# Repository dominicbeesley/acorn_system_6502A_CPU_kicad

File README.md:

# acorn_system_6502A_CPU_kicad
 Acorn System 6502A clone card

 This is a clone of the Acorn 6502A 1/2/3 MHz card for the System Microcomputer range.

 It is not a perfect copy:
 - some routing (especially on the front copper plane) is not a perfect copy
 - some "extra wiggles" on the Acorn card have not been copied
 - some fixes have been added (see below)

It is intended that as it stands this is a drop-in replacement for the original card. If the fix jumpers are left alone then it should function identically.

# Fixes

Two extra decoupling capacitors and some extra routing has been added. C10 is added close to the CPU. Another C11 is close to IC12, for this to be effective an extra wire may need to be added on the underside of the board to connect VCC direct to the capacitor. It is not clear whether either of these are necessary but some pictures show an extra capacitor tacked onto IC12.

## CPU card always to Generate data stobes

On the original card the NRDS and NWDS data strobe signals are not always generated by the CPU card but are set to tri-state when the bus is granted to another card. This would require any DMA card to contains identical circuitry to the CPU card. An optional link LKD1 can be cut and re-made to have the CPU card always generate these signals.

## Data buffer direction on bus grant

There is seemingly a bug in the original card in that the direction is not reversed when the bus is granted and local (to the CPU card) resources are being accessed by another bus master. (The buffer enable signal _is_ however correctly reversed)

LKD2 if broken and remade will enable the buffer direction to be reversed. This should allow local resources (ROM, 6116, VIA) to be accessed by alternative bus masters.

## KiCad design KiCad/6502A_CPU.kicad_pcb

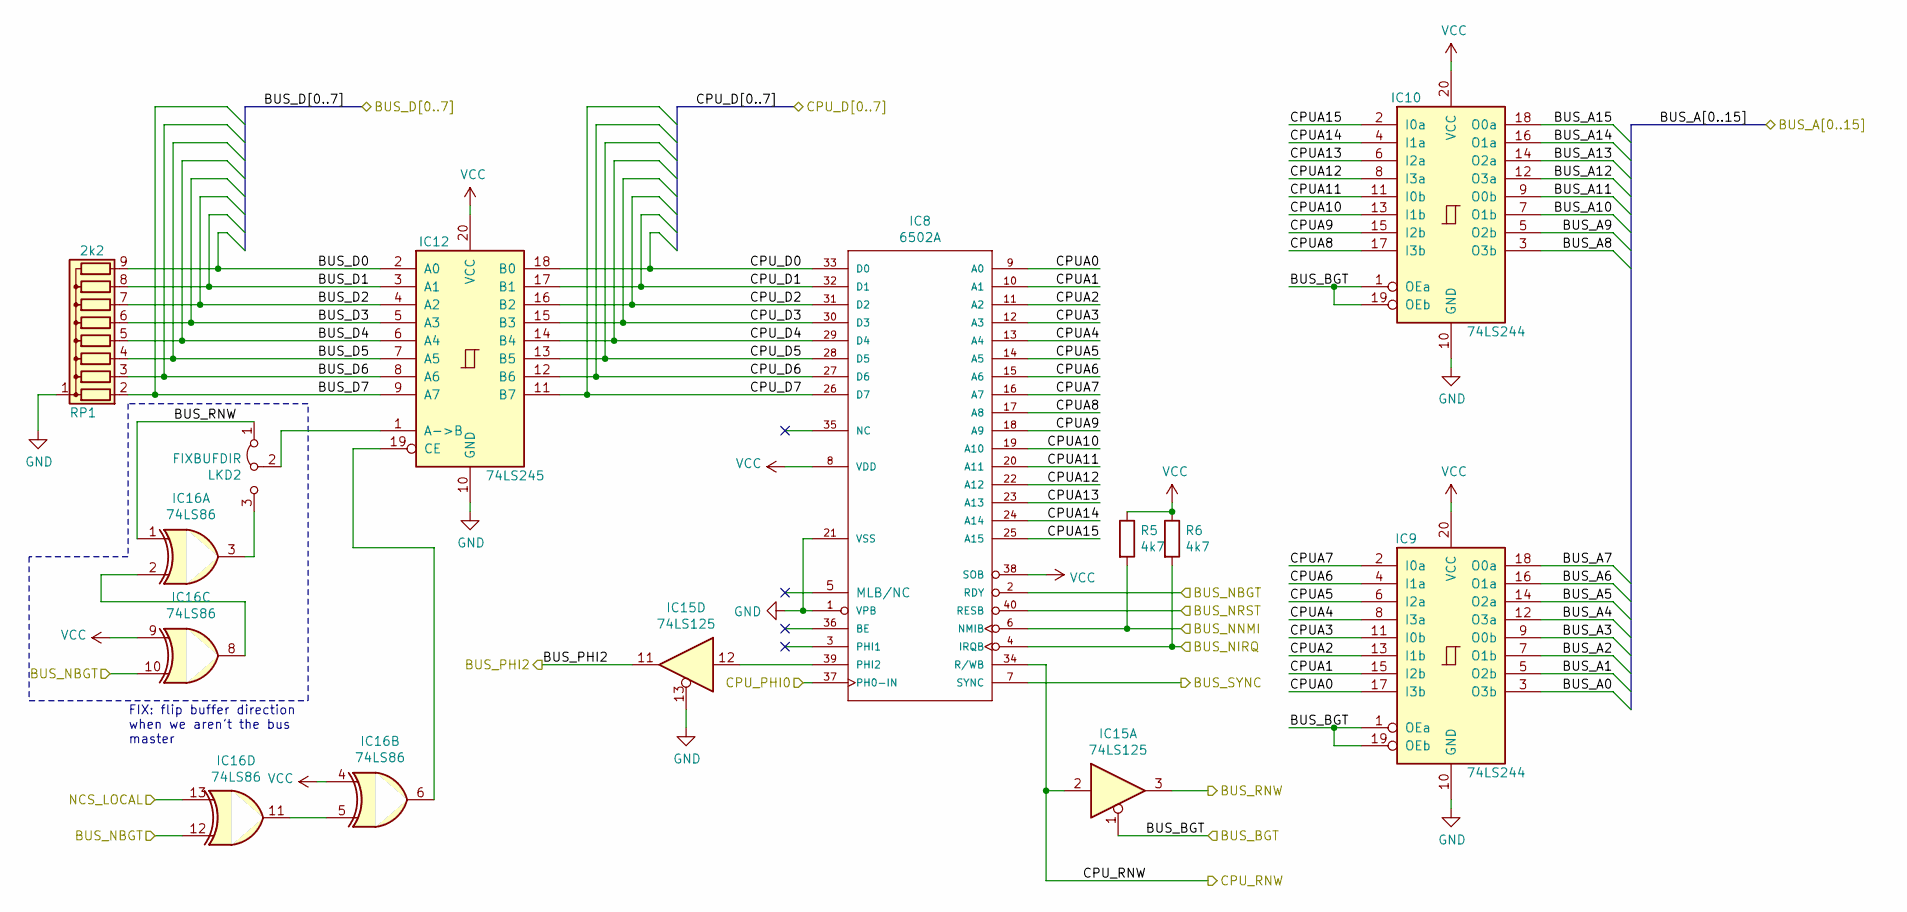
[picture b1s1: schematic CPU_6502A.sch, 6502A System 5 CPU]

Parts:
IC8: 6502A; DIP-40_W15.24mm_Socket
IC9, IC10: 74LS244; DIP-20_W7.62mm_Socket
IC12: 74LS245; DIP-20_W7.62mm_Socket
IC15: 74LS125; DIP-14_W7.62mm_Socket
IC16: 74LS86; DIP-14_W7.62mm_Socket
LKD2: FIXBUFDIR; Pin_Header_Straight_1x03_Pitch2.54mm_tight_NC12
R5, R6: 4k7; R_Axial_DIN0309_L9.0mm_D2.0mm_P12.70mm_Horizontal
RP1: 2k2; R_Array_SIP9

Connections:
/BUS_NBGT: IC8.2 (RDY), IC16.10, IC16.12; also elsewhere on the board
/BUS_NIRQ: IC8.4 (IRQB), R6.2; also elsewhere on the board
/BUS_NNMI: IC8.6 (NMIB), R5.2; also elsewhere on the board
/BUS_NRST: IC8.40 (RESB); also elsewhere on the board
/BUS_PHI2: IC15.11; also elsewhere on the board
/BUS_RNW: IC15.3, IC16.1, LKD2.1 (A); also elsewhere on the board
/BUS_SYNC: IC8.7 (SYNC); also elsewhere on the board
/CPU_6502A/BUS_A0: IC9.3 (O3b); also elsewhere on the board
/CPU_6502A/BUS_A1: IC9.5 (O2b); also elsewhere on the board
/CPU_6502A/BUS_A2: IC9.7 (O1b); also elsewhere on the board
/CPU_6502A/BUS_A3: IC9.9 (O0b); also elsewhere on the board
/CPU_6502A/BUS_A4: IC9.12 (O3a); also elsewhere on the board
/CPU_6502A/BUS_A5: IC9.14 (O2a); also elsewhere on the board
/CPU_6502A/BUS_A6: IC9.16 (O1a); also elsewhere on the board
/CPU_6502A/BUS_A7: IC9.18 (O0a); also elsewhere on the board
/CPU_6502A/BUS_A8: IC10.3 (O3b); also elsewhere on the board
/CPU_6502A/BUS_A9: IC10.5 (O2b); also elsewhere on the board
/CPU_6502A/BUS_A10: IC10.7 (O1b); also elsewhere on the board
/CPU_6502A/BUS_A11: IC10.9 (O0b); also elsewhere on the board
/CPU_6502A/BUS_A12: IC10.12 (O3a); also elsewhere on the board
/CPU_6502A/BUS_A13: IC10.14 (O2a); also elsewhere on the board
/CPU_6502A/BUS_A14: IC10.16 (O1a); also elsewhere on the board
/CPU_6502A/BUS_A15: IC10.18 (O0a); also elsewhere on the board
/CPU_6502A/BUS_BGT: IC9.1 (OEa), IC9.19 (OEb), IC10.1 (OEa), IC10.19 (OEb), IC15.1; also elsewhere on the board
/CPU_6502A/BUS_D0: IC12.2 (A0), RP1.9 (R8); also elsewhere on the board
/CPU_6502A/BUS_D1: IC12.3 (A1), RP1.8 (R7); also elsewhere on the board
/CPU_6502A/BUS_D2: IC12.4 (A2), RP1.7 (R6); also elsewhere on the board
/CPU_6502A/BUS_D3: IC12.5 (A3), RP1.6 (R5); also elsewhere on the board
/CPU_6502A/BUS_D4: IC12.6 (A4), RP1.5 (R4); also elsewhere on the board
/CPU_6502A/BUS_D5: IC12.7 (A5), RP1.4 (R3); also elsewhere on the board
/CPU_6502A/BUS_D6: IC12.8 (A6), RP1.3 (R2); also elsewhere on the board
/CPU_6502A/BUS_D7: IC12.9 (A7), RP1.2 (R1); also elsewhere on the board
/CPU_6502A/CPUA0: IC8.9 (A0), IC9.17 (I3b)
/CPU_6502A/CPUA1: IC8.10 (A1), IC9.15 (I2b)
/CPU_6502A/CPUA2: IC8.11 (A2), IC9.13 (I1b)
/CPU_6502A/CPUA3: IC8.12 (A3), IC9.11 (I0b)
/CPU_6502A/CPUA4: IC8.13 (A4), IC9.8 (I3a)
/CPU_6502A/CPUA5: IC8.14 (A5), IC9.6 (I2a)
/CPU_6502A/CPUA6: IC8.15 (A6), IC9.4 (I1a)
/CPU_6502A/CPUA7: IC8.16 (A7), IC9.2 (I0a)
/CPU_6502A/CPUA8: IC8.17 (A8), IC10.17 (I3b)
/CPU_6502A/CPUA9: IC8.18 (A9), IC10.15 (I2b)
/CPU_6502A/CPUA10: IC8.19 (A10), IC10.13 (I1b)
/CPU_6502A/CPUA11: IC8.20 (A11), IC10.11 (I0b)
/CPU_6502A/CPUA12: IC8.22 (A12), IC10.8 (I3a)
/CPU_6502A/CPUA13: IC8.23 (A13), IC10.6 (I2a)
/CPU_6502A/CPUA14: IC8.24 (A14), IC10.4 (I1a)
/CPU_6502A/CPUA15: IC8.25 (A15), IC10.2 (I0a)
/CPU_6502A/CPU_D0: IC8.33 (D0), IC12.18 (B0); also elsewhere on the board
/CPU_6502A/CPU_D1: IC8.32 (D1), IC12.17 (B1); also elsewhere on the board
/CPU_6502A/CPU_D2: IC8.31 (D2), IC12.16 (B2); also elsewhere on the board
/CPU_6502A/CPU_D3: IC8.30 (D3), IC12.15 (B3); also elsewhere on the board
/CPU_6502A/CPU_D4: IC8.29 (D4), IC12.14 (B4); also elsewhere on the board
/CPU_6502A/CPU_D5: IC8.28 (D5), IC12.13 (B5); also elsewhere on the board
/CPU_6502A/CPU_D6: IC8.27 (D6), IC12.12 (B6); also elsewhere on the board
/CPU_6502A/CPU_D7: IC8.26 (D7), IC12.11 (B7); also elsewhere on the board
/CPU_6502A/CPU_RNW: IC8.34 (R/WB), IC15.2; also elsewhere on the board
/CPU_6502A/NCS_LOCAL: IC16.13; also elsewhere on the board
/CPU_READY/CPU_CLK_PHI0: IC8.37 (PH0-IN); also elsewhere on the board
GND: IC8.1 (VPB), IC8.21 (VSS), IC9.10 (GND), IC10.10 (GND), IC12.10 (GND), IC15.13, RP1.1 (common); also elsewhere on the board
unnamed: IC12.1 (A->B), LKD2.2 (C)
unnamed: IC12.19 (CE), IC16.6
unnamed: IC8.39 (PHI2), IC15.12
unnamed: IC16.2, IC16.8
unnamed: IC16.3, LKD2.3 (B)
unnamed: IC16.5, IC16.11
VCC: IC8.8 (VDD), IC8.38 (SOB), IC9.20 (VCC), IC10.20 (VCC), IC12.20 (VCC), IC16.4, IC16.9, R5.1, R6.1; also elsewhere on the board

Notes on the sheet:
FIX: flip buffer direction when we aren't the bus master

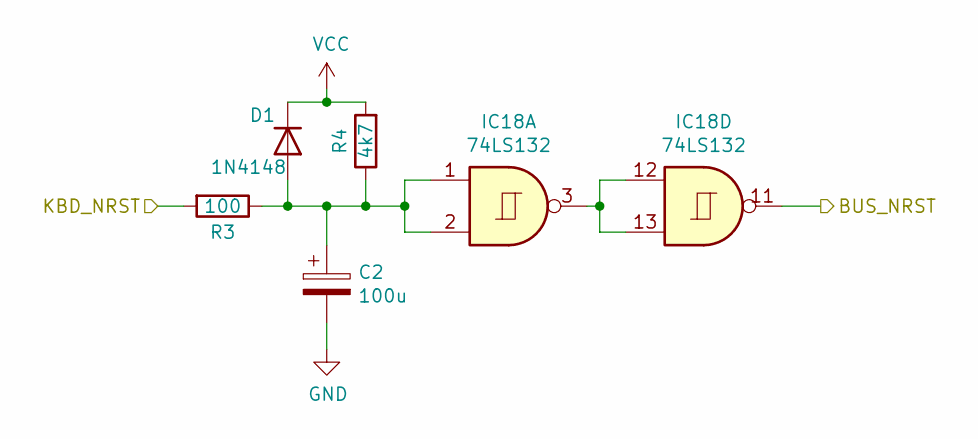
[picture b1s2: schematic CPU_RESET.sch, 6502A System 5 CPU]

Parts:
C2: 100u; C_Disc_D5.1mm_W3.2mm_P5.00mm
D1: 1N4148; D_DO-35_SOD27_P7.62mm_Horizontal
IC18: 74LS132; DIP-14_W7.62mm_Socket
R3: 100; R_Axial_DIN0309_L9.0mm_D2.0mm_P12.70mm_Horizontal
R4: 4k7; R_Axial_DIN0309_L9.0mm_D2.0mm_P12.70mm_Horizontal

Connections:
/BUS_NRST: IC18.11; also elsewhere on the board
/CPU_RESET/KBD_NRST: R3.2; also elsewhere on the board
GND: C2.2; also elsewhere on the board
unnamed: C2.1, D1.2 (A), IC18.1, IC18.2, R3.1, R4.1
unnamed: IC18.3, IC18.12, IC18.13
VCC: D1.1 (K), R4.2; also elsewhere on the board

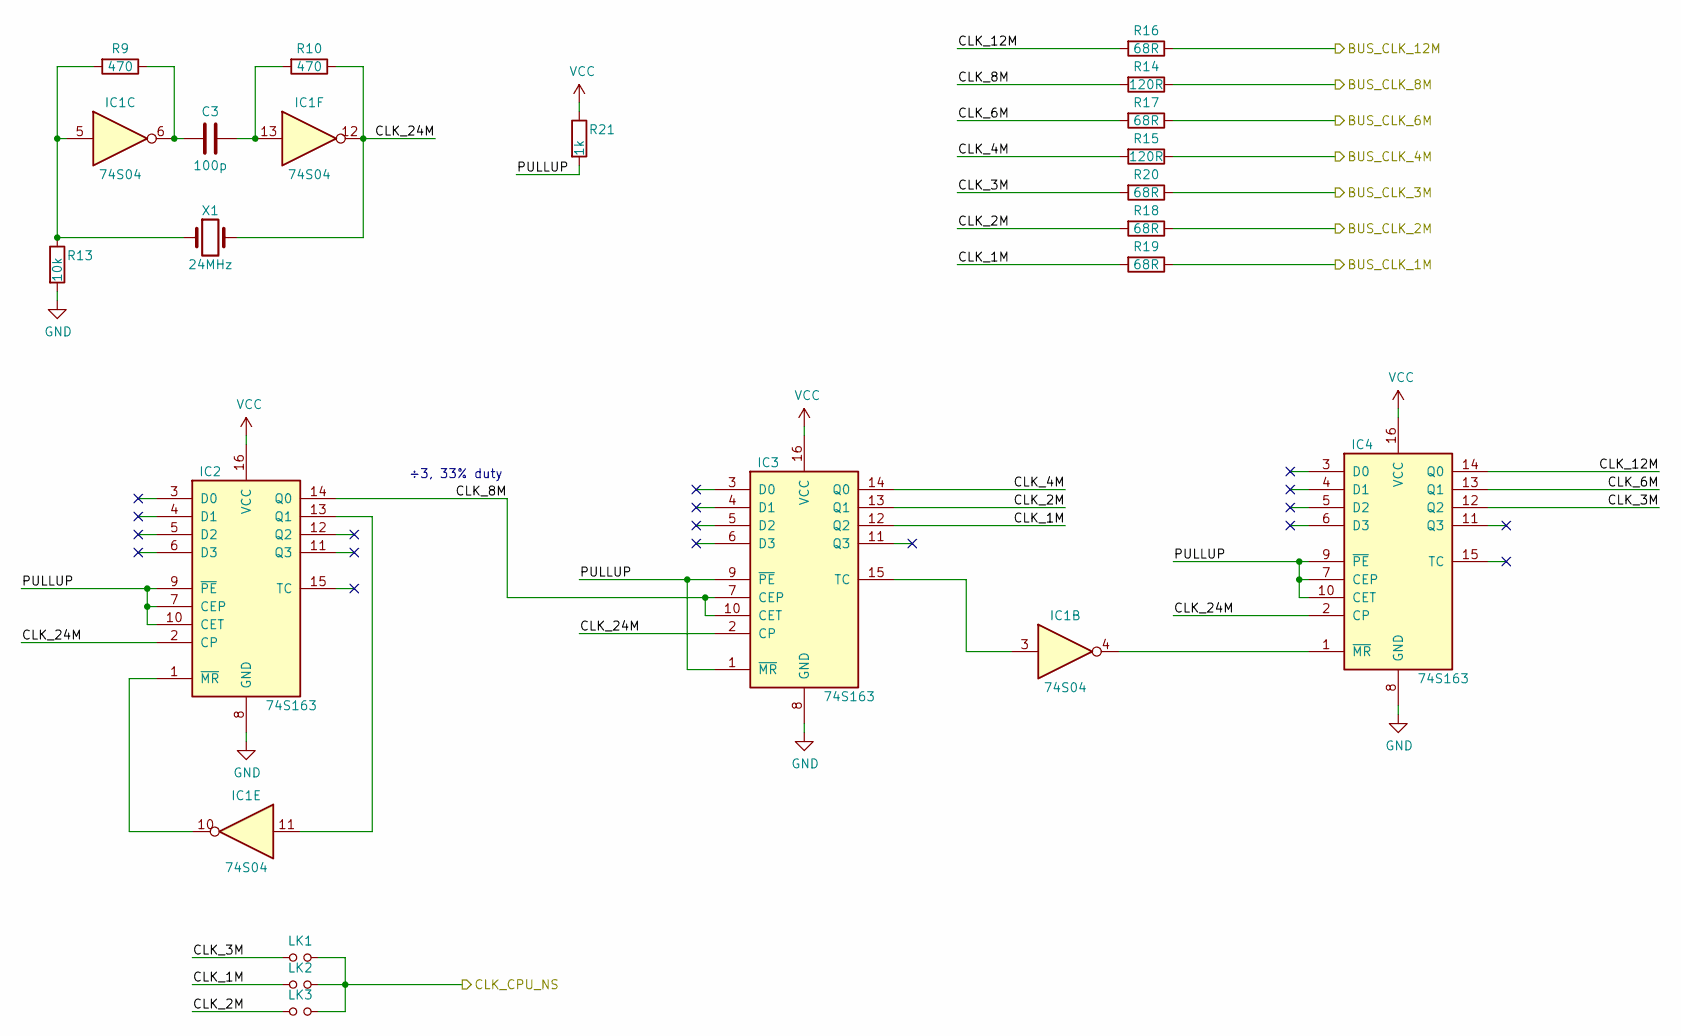
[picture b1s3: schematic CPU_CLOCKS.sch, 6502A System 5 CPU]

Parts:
C3: 100p; C_Disc_D5.0mm_W2.5mm_P2.50mm
IC1: 74S04; DIP-14_W7.62mm_Socket
IC2, IC3, IC4: 74S163; DIP-16_W7.62mm_Socket
LK1, LK2, LK3: Jumper_NO_Small; Pin_Header_Straight_1x02_Pitch2.54mm-tight
R9: 470; R_Axial_DIN0207_L6.3mm_D2.5mm_P2.54mm_Vertical
R10: 470; R_Axial_DIN0309_L9.0mm_D2.0mm_P12.70mm_Horizontal
R13: 10k; R_Axial_DIN0309_L9.0mm_D2.0mm_P12.70mm_Horizontal
R14, R15: 120R; R_Axial_DIN0207_L6.3mm_D2.5mm_P2.54mm_Vertical
R16, R17, R18, R19, R20: 68R; R_Axial_DIN0207_L6.3mm_D2.5mm_P2.54mm_Vertical
R21: 1k; R_Axial_DIN0309_L9.0mm_D2.0mm_P12.70mm_Horizontal
X1: 24MHz; Resonator-2pin_w8.0mm_h3.5mm

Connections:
/BUS_CLK_1M: R19.1; also elsewhere on the board
/BUS_CLK_2M: R18.1; also elsewhere on the board
/BUS_CLK_3M: R20.1; also elsewhere on the board
/BUS_CLK_4M: R15.1; also elsewhere on the board
/BUS_CLK_6M: R17.1; also elsewhere on the board
/BUS_CLK_8M: R14.1; also elsewhere on the board
/BUS_CLK_12M: R16.1; also elsewhere on the board
/CPU_CLOCKS/CLK_1M: IC3.12 (Q2), LK2.1, R19.2
/CPU_CLOCKS/CLK_2M: IC3.13 (Q1), LK3.1, R18.2
/CPU_CLOCKS/CLK_3M: IC4.12 (Q2), LK1.1, R20.2
/CPU_CLOCKS/CLK_4M: IC3.14 (Q0), R15.2
/CPU_CLOCKS/CLK_6M: IC4.13 (Q1), R17.2
/CPU_CLOCKS/CLK_8M: IC2.14 (Q0), IC3.7 (CEP), IC3.10 (CET), R14.2
/CPU_CLOCKS/CLK_12M: IC4.14 (Q0), R16.2
/CPU_CLOCKS/CLK_24M: IC1.12, IC2.2 (CP), IC3.2 (CP), IC4.2 (CP), R10.1, X1.2
/CPU_CLOCKS/CLK_CPU_NS: LK1.2, LK2.2, LK3.2; also elsewhere on the board
/CPU_CLOCKS/PULLUP: IC2.7 (CEP), IC2.9 (~PE), IC2.10 (CET), IC3.1 (~MR), IC3.9 (~PE), IC4.7 (CEP), IC4.9 (~PE), IC4.10 (CET), R21.2
GND: IC2.8 (GND), IC3.8 (GND), IC4.8 (GND), R13.2; also elsewhere on the board
unnamed: C3.1, IC1.13, R10.2
unnamed: C3.2, IC1.6, R9.1
unnamed: IC1.3, IC3.15 (TC)
unnamed: IC1.4, IC4.1 (~MR)
unnamed: IC1.5, R9.2, R13.1, X1.1
unnamed: IC1.10, IC2.1 (~MR)
unnamed: IC1.11, IC2.13 (Q1)
VCC: IC2.16 (VCC), IC3.16 (VCC), IC4.16 (VCC), R21.1; also elsewhere on the board

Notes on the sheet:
÷3, 33% duty

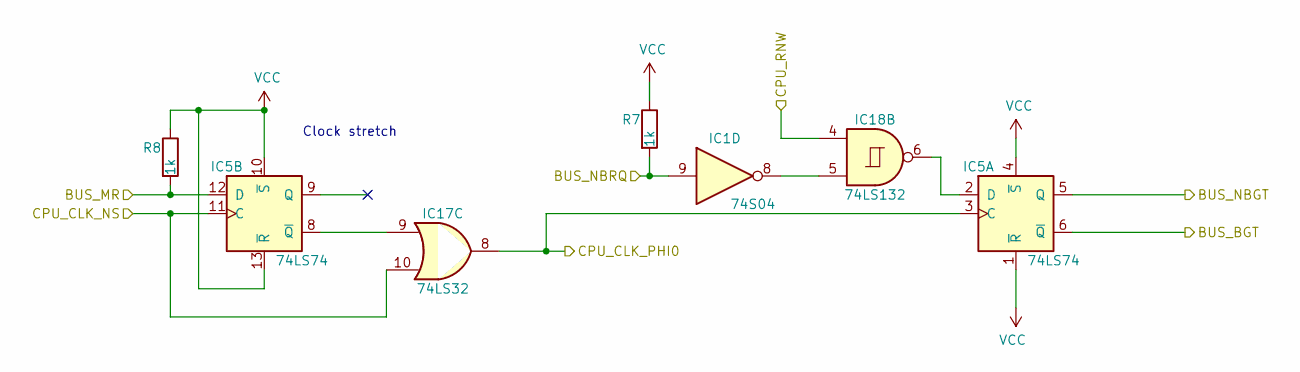
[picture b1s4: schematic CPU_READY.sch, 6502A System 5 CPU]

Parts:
IC1: 74S04; DIP-14_W7.62mm_Socket
IC5: 74LS74; DIP-14_W7.62mm_Socket
IC17: 74LS32; DIP-14_W7.62mm_Socket
IC18: 74LS132; DIP-14_W7.62mm_Socket
R7, R8: 1k; R_Axial_DIN0309_L9.0mm_D2.0mm_P12.70mm_Horizontal

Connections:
/BUS_MR: IC5.12 (D), R8.2; also elsewhere on the board
/BUS_NBGT: IC5.5 (Q); also elsewhere on the board
/BUS_NBRQ: IC1.9, R7.2; also elsewhere on the board
/CPU_6502A/BUS_BGT: IC5.6 (~Q); also elsewhere on the board
/CPU_6502A/CPU_RNW: IC18.4; also elsewhere on the board
/CPU_CLOCKS/CLK_CPU_NS: IC5.11 (C), IC17.10; also elsewhere on the board
/CPU_READY/CPU_CLK_PHI0: IC5.3 (C), IC17.8; also elsewhere on the board
unnamed: IC1.8, IC18.5
unnamed: IC5.8 (~Q), IC17.9
unnamed: IC5.2 (D), IC18.6
VCC: IC5.1 (~R), IC5.4 (~S), IC5.10 (~S), IC5.13 (~R), R7.1, R8.1; also elsewhere on the board

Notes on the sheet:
Clock stretch

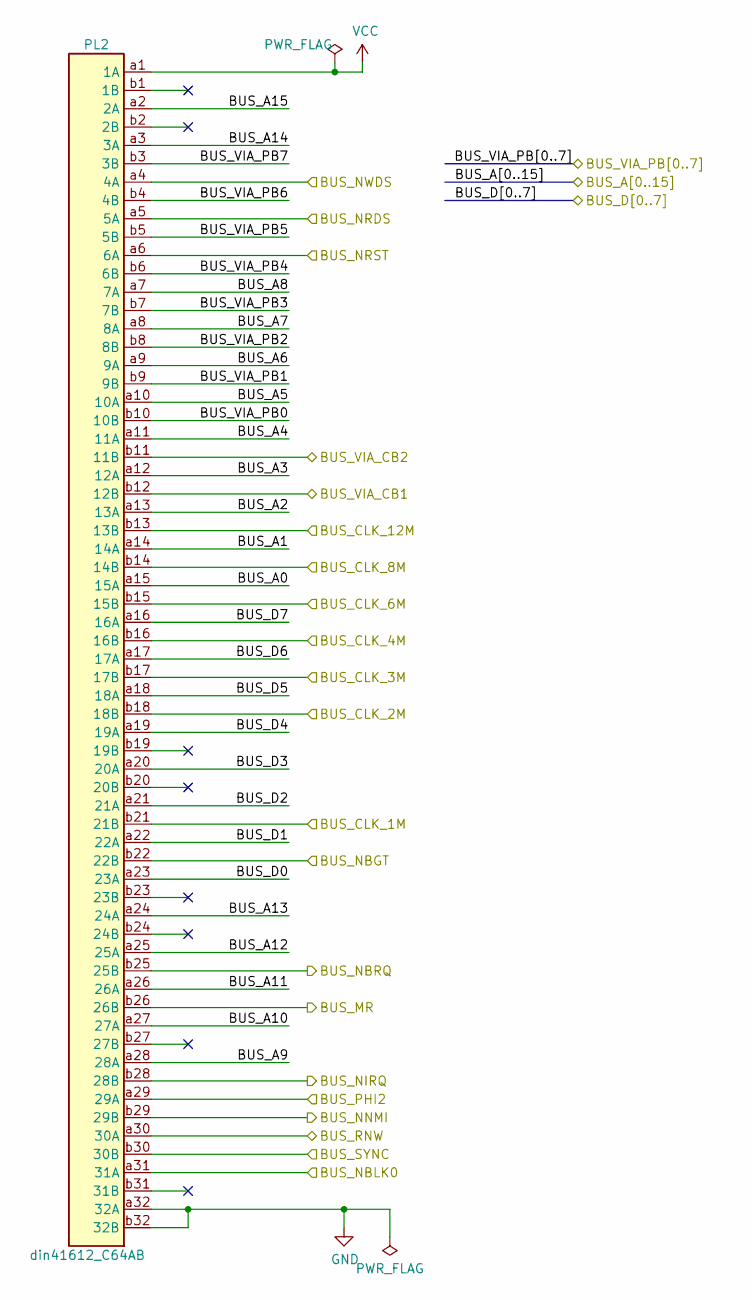
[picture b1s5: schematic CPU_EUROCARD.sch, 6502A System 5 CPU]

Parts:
PL2: din41612_C64AB; DIN41612_B_2x32_Male_Horizontal_THT

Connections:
/BUS_CLK_1M: PL2.b21 (21B); also elsewhere on the board
/BUS_CLK_2M: PL2.b18 (18B); also elsewhere on the board
/BUS_CLK_3M: PL2.b17 (17B); also elsewhere on the board
/BUS_CLK_4M: PL2.b16 (16B); also elsewhere on the board
/BUS_CLK_6M: PL2.b15 (15B); also elsewhere on the board
/BUS_CLK_8M: PL2.b14 (14B); also elsewhere on the board
/BUS_CLK_12M: PL2.b13 (13B); also elsewhere on the board
/BUS_MR: PL2.b26 (26B); also elsewhere on the board
/BUS_NBGT: PL2.b22 (22B); also elsewhere on the board
/BUS_NBLK0: PL2.a31 (31A); also elsewhere on the board
/BUS_NBRQ: PL2.b25 (25B); also elsewhere on the board
/BUS_NIRQ: PL2.b28 (28B); also elsewhere on the board
/BUS_NNMI: PL2.b29 (29B); also elsewhere on the board
/BUS_NRDS: PL2.a5 (5A); also elsewhere on the board
/BUS_NRST: PL2.a6 (6A); also elsewhere on the board
/BUS_NWDS: PL2.a4 (4A); also elsewhere on the board
/BUS_PHI2: PL2.a29 (29A); also elsewhere on the board
/BUS_RNW: PL2.a30 (30A); also elsewhere on the board
/BUS_SYNC: PL2.b30 (30B); also elsewhere on the board
/BUS_VIA_CB1: PL2.b12 (12B); also elsewhere on the board
/BUS_VIA_CB2: PL2.b11 (11B); also elsewhere on the board
/CPU_6502A/BUS_A0: PL2.a15 (15A); also elsewhere on the board
/CPU_6502A/BUS_A1: PL2.a14 (14A); also elsewhere on the board
/CPU_6502A/BUS_A2: PL2.a13 (13A); also elsewhere on the board
/CPU_6502A/BUS_A3: PL2.a12 (12A); also elsewhere on the board
/CPU_6502A/BUS_A4: PL2.a11 (11A); also elsewhere on the board
/CPU_6502A/BUS_A5: PL2.a10 (10A); also elsewhere on the board
/CPU_6502A/BUS_A6: PL2.a9 (9A); also elsewhere on the board
/CPU_6502A/BUS_A7: PL2.a8 (8A); also elsewhere on the board
/CPU_6502A/BUS_A8: PL2.a7 (7A); also elsewhere on the board
/CPU_6502A/BUS_A9: PL2.a28 (28A); also elsewhere on the board
/CPU_6502A/BUS_A10: PL2.a27 (27A); also elsewhere on the board
/CPU_6502A/BUS_A11: PL2.a26 (26A); also elsewhere on the board
/CPU_6502A/BUS_A12: PL2.a25 (25A); also elsewhere on the board
/CPU_6502A/BUS_A13: PL2.a24 (24A); also elsewhere on the board
/CPU_6502A/BUS_A14: PL2.a3 (3A); also elsewhere on the board
/CPU_6502A/BUS_A15: PL2.a2 (2A); also elsewhere on the board
/CPU_6502A/BUS_D0: PL2.a23 (23A); also elsewhere on the board
/CPU_6502A/BUS_D1: PL2.a22 (22A); also elsewhere on the board
/CPU_6502A/BUS_D2: PL2.a21 (21A); also elsewhere on the board
/CPU_6502A/BUS_D3: PL2.a20 (20A); also elsewhere on the board
/CPU_6502A/BUS_D4: PL2.a19 (19A); also elsewhere on the board
/CPU_6502A/BUS_D5: PL2.a18 (18A); also elsewhere on the board
/CPU_6502A/BUS_D6: PL2.a17 (17A); also elsewhere on the board
/CPU_6502A/BUS_D7: PL2.a16 (16A); also elsewhere on the board
/CPU_EUROCARD/BUS_VIA_PB0: PL2.b10 (10B); also elsewhere on the board
/CPU_EUROCARD/BUS_VIA_PB1: PL2.b9 (9B); also elsewhere on the board
/CPU_EUROCARD/BUS_VIA_PB2: PL2.b8 (8B); also elsewhere on the board
/CPU_EUROCARD/BUS_VIA_PB3: PL2.b7 (7B); also elsewhere on the board
/CPU_EUROCARD/BUS_VIA_PB4: PL2.b6 (6B); also elsewhere on the board
/CPU_EUROCARD/BUS_VIA_PB5: PL2.b5 (5B); also elsewhere on the board
/CPU_EUROCARD/BUS_VIA_PB6: PL2.b4 (4B); also elsewhere on the board
/CPU_EUROCARD/BUS_VIA_PB7: PL2.b3 (3B); also elsewhere on the board
GND: PL2.a32 (32A), PL2.b32 (32B); also elsewhere on the board
VCC: PL2.a1 (1A); also elsewhere on the board

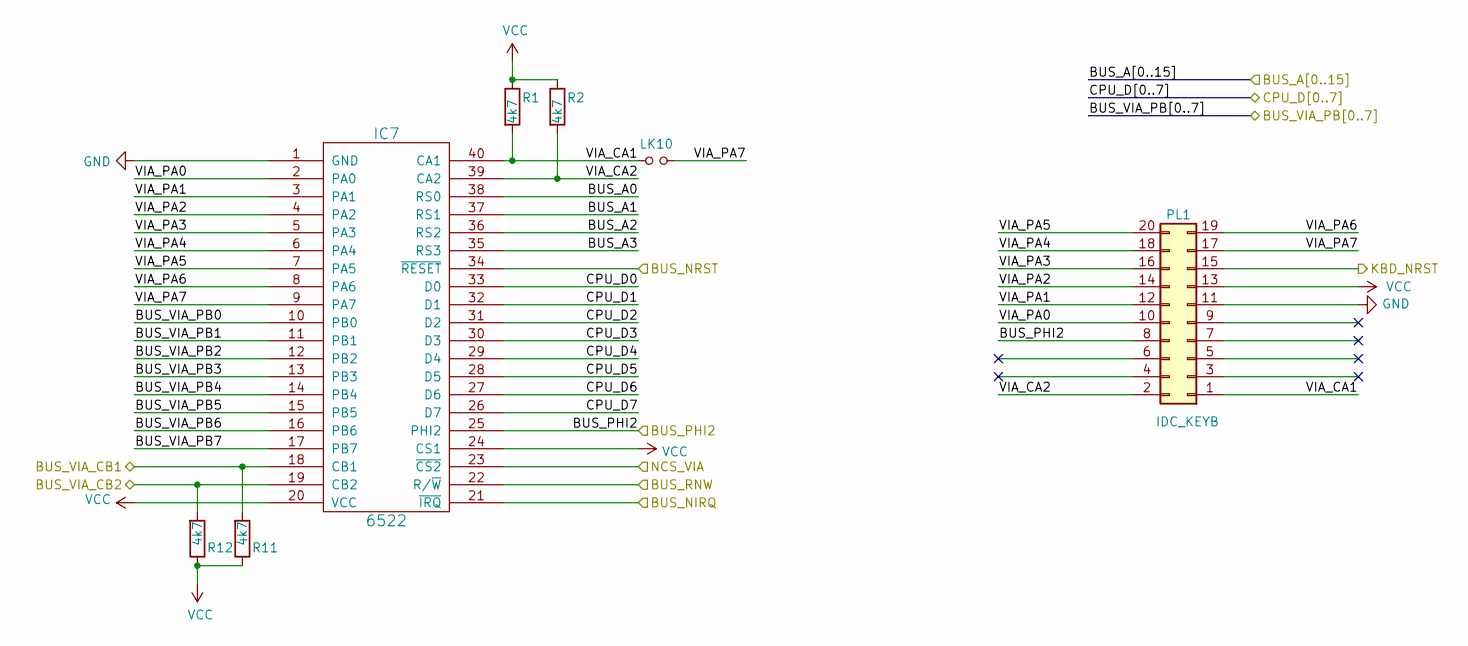
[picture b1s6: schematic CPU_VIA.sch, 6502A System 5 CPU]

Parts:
IC7: 6522; DIP-40_W15.24mm_Socket
LK10: Jumper_NO_Small; Pin_Header_Straight_1x02_Pitch2.54mm-tight
PL1: IDC_KEYB; IDC-Header_2x10_P2.54mm_Horizontal_Lock_noholes
R1, R2, R11, R12: 4k7; R_Axial_DIN0309_L9.0mm_D2.0mm_P12.70mm_Horizontal

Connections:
/BUS_NIRQ: IC7.21 (~IRQ); also elsewhere on the board
/BUS_NRST: IC7.34 (~RESET); also elsewhere on the board
/BUS_PHI2: IC7.25 (PHI2), PL1.8; also elsewhere on the board
/BUS_RNW: IC7.22 (R/~W); also elsewhere on the board
/BUS_VIA_CB1: IC7.18 (CB1), R11.2; also elsewhere on the board
/BUS_VIA_CB2: IC7.19 (CB2), R12.2; also elsewhere on the board
/CPU_6502A/BUS_A0: IC7.38 (RS0); also elsewhere on the board
/CPU_6502A/BUS_A1: IC7.37 (RS1); also elsewhere on the board
/CPU_6502A/BUS_A2: IC7.36 (RS2); also elsewhere on the board
/CPU_6502A/BUS_A3: IC7.35 (RS3); also elsewhere on the board
/CPU_6502A/CPU_D0: IC7.33 (D0); also elsewhere on the board
/CPU_6502A/CPU_D1: IC7.32 (D1); also elsewhere on the board
/CPU_6502A/CPU_D2: IC7.31 (D2); also elsewhere on the board
/CPU_6502A/CPU_D3: IC7.30 (D3); also elsewhere on the board
/CPU_6502A/CPU_D4: IC7.29 (D4); also elsewhere on the board
/CPU_6502A/CPU_D5: IC7.28 (D5); also elsewhere on the board
/CPU_6502A/CPU_D6: IC7.27 (D6); also elsewhere on the board
/CPU_6502A/CPU_D7: IC7.26 (D7); also elsewhere on the board
/CPU_DEVSEL/NCS_VIA: IC7.23 (~CS2); also elsewhere on the board
/CPU_EUROCARD/BUS_VIA_PB0: IC7.10 (PB0); also elsewhere on the board
/CPU_EUROCARD/BUS_VIA_PB1: IC7.11 (PB1); also elsewhere on the board
/CPU_EUROCARD/BUS_VIA_PB2: IC7.12 (PB2); also elsewhere on the board
/CPU_EUROCARD/BUS_VIA_PB3: IC7.13 (PB3); also elsewhere on the board
/CPU_EUROCARD/BUS_VIA_PB4: IC7.14 (PB4); also elsewhere on the board
/CPU_EUROCARD/BUS_VIA_PB5: IC7.15 (PB5); also elsewhere on the board
/CPU_EUROCARD/BUS_VIA_PB6: IC7.16 (PB6); also elsewhere on the board
/CPU_EUROCARD/BUS_VIA_PB7: IC7.17 (PB7); also elsewhere on the board
/CPU_RESET/KBD_NRST: PL1.15; also elsewhere on the board
/CPU_VIA/VIA_CA1: IC7.40 (CA1), LK10.1, PL1.1, R1.2
/CPU_VIA/VIA_CA2: IC7.39 (CA2), PL1.2, R2.2
/CPU_VIA/VIA_PA0: IC7.2 (PA0), PL1.10
/CPU_VIA/VIA_PA1: IC7.3 (PA1), PL1.12
/CPU_VIA/VIA_PA2: IC7.4 (PA2), PL1.14
/CPU_VIA/VIA_PA3: IC7.5 (PA3), PL1.16
/CPU_VIA/VIA_PA4: IC7.6 (PA4), PL1.18
/CPU_VIA/VIA_PA5: IC7.7 (PA5), PL1.20
/CPU_VIA/VIA_PA6: IC7.8 (PA6), PL1.19
/CPU_VIA/VIA_PA7: IC7.9 (PA7), LK10.2, PL1.17
GND: IC7.1 (GND), PL1.11; also elsewhere on the board
VCC: IC7.20 (VCC), IC7.24 (CS1), PL1.13, R1.1, R2.1, R11.1, R12.1; also elsewhere on the board

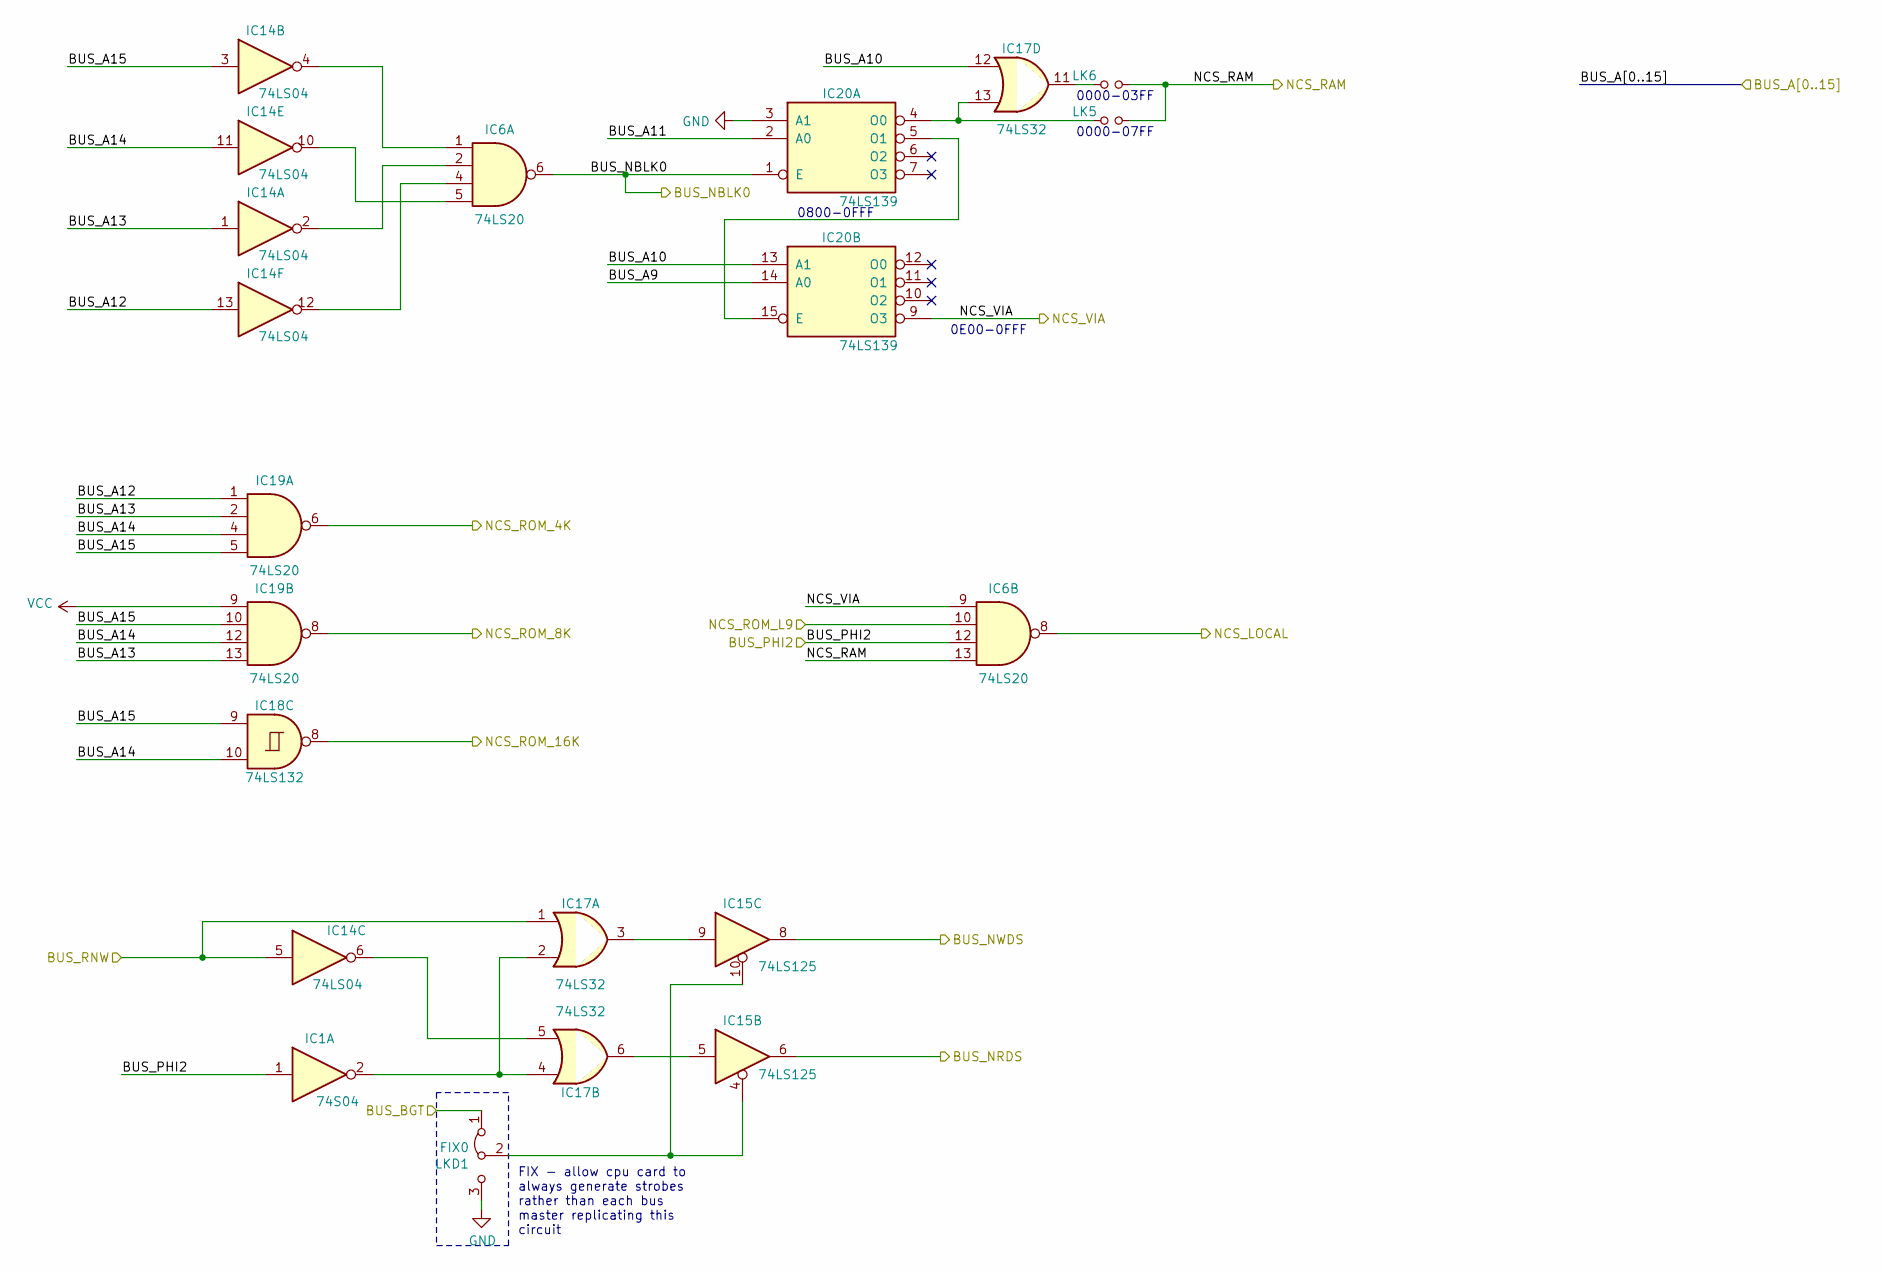
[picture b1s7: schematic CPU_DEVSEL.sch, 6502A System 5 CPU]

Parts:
IC1: 74S04; DIP-14_W7.62mm_Socket
IC6, IC19: 74LS20; DIP-14_W7.62mm_Socket
IC14: 74LS04; DIP-14_W7.62mm_Socket
IC15: 74LS125; DIP-14_W7.62mm_Socket
IC17: 74LS32; DIP-14_W7.62mm_Socket
IC18: 74LS132; DIP-14_W7.62mm_Socket
IC20: 74LS139; DIP-16_W7.62mm_Socket
LK5, LK6: Jumper_NO_Small; Pin_Header_Straight_1x02_Pitch2.54mm-tight
LKD1: FIX0; Pin_Header_Straight_1x03_Pitch2.54mm_tight_NC12

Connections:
/BUS_NBLK0: IC6.6, IC20.1 (E); also elsewhere on the board
/BUS_NRDS: IC15.6; also elsewhere on the board
/BUS_NWDS: IC15.8; also elsewhere on the board
/BUS_PHI2: IC1.1, IC6.12; also elsewhere on the board
/BUS_RNW: IC14.5, IC17.1; also elsewhere on the board
/CPU_6502A/BUS_A9: IC20.14 (A0); also elsewhere on the board
/CPU_6502A/BUS_A10: IC17.12, IC20.13 (A1); also elsewhere on the board
/CPU_6502A/BUS_A11: IC20.2 (A0); also elsewhere on the board
/CPU_6502A/BUS_A12: IC14.13, IC19.1; also elsewhere on the board
/CPU_6502A/BUS_A13: IC14.1, IC19.2, IC19.13; also elsewhere on the board
/CPU_6502A/BUS_A14: IC14.11, IC18.10, IC19.4, IC19.12; also elsewhere on the board
/CPU_6502A/BUS_A15: IC14.3, IC18.9, IC19.5, IC19.10; also elsewhere on the board
/CPU_6502A/BUS_BGT: LKD1.1 (A); also elsewhere on the board
/CPU_6502A/NCS_LOCAL: IC6.8; also elsewhere on the board
/CPU_DEVSEL/NCS_RAM: IC6.13, LK5.2, LK6.2; also elsewhere on the board
/CPU_DEVSEL/NCS_ROM_4K: IC19.6; also elsewhere on the board
/CPU_DEVSEL/NCS_ROM_8K: IC19.8; also elsewhere on the board
/CPU_DEVSEL/NCS_ROM_16K: IC18.8; also elsewhere on the board
/CPU_DEVSEL/NCS_ROM_L9: IC6.10; also elsewhere on the board
/CPU_DEVSEL/NCS_VIA: IC6.9, IC20.9 (O3); also elsewhere on the board
GND: IC20.3 (A1), LKD1.3 (B); also elsewhere on the board
unnamed: IC1.2, IC17.2, IC17.4
unnamed: IC6.2, IC14.2
unnamed: IC6.1, IC14.4
unnamed: IC14.6, IC17.5
unnamed: IC6.5, IC14.10
unnamed: IC6.4, IC14.12
unnamed: IC15.5, IC17.6
unnamed: IC15.9, IC17.3
unnamed: IC15.4, IC15.10, LKD1.2 (C)
unnamed: IC17.11, LK6.1
unnamed: IC17.13, IC20.4 (O0), LK5.1
unnamed: IC20.5 (O1), IC20.15 (E)
VCC: IC19.9; also elsewhere on the board

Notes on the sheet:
0000-07FF
0000-03FF
0800-0FFF
0E00-0FFF
FIX - allow cpu card to always generate strobes rather than each bus master replicating this circuit

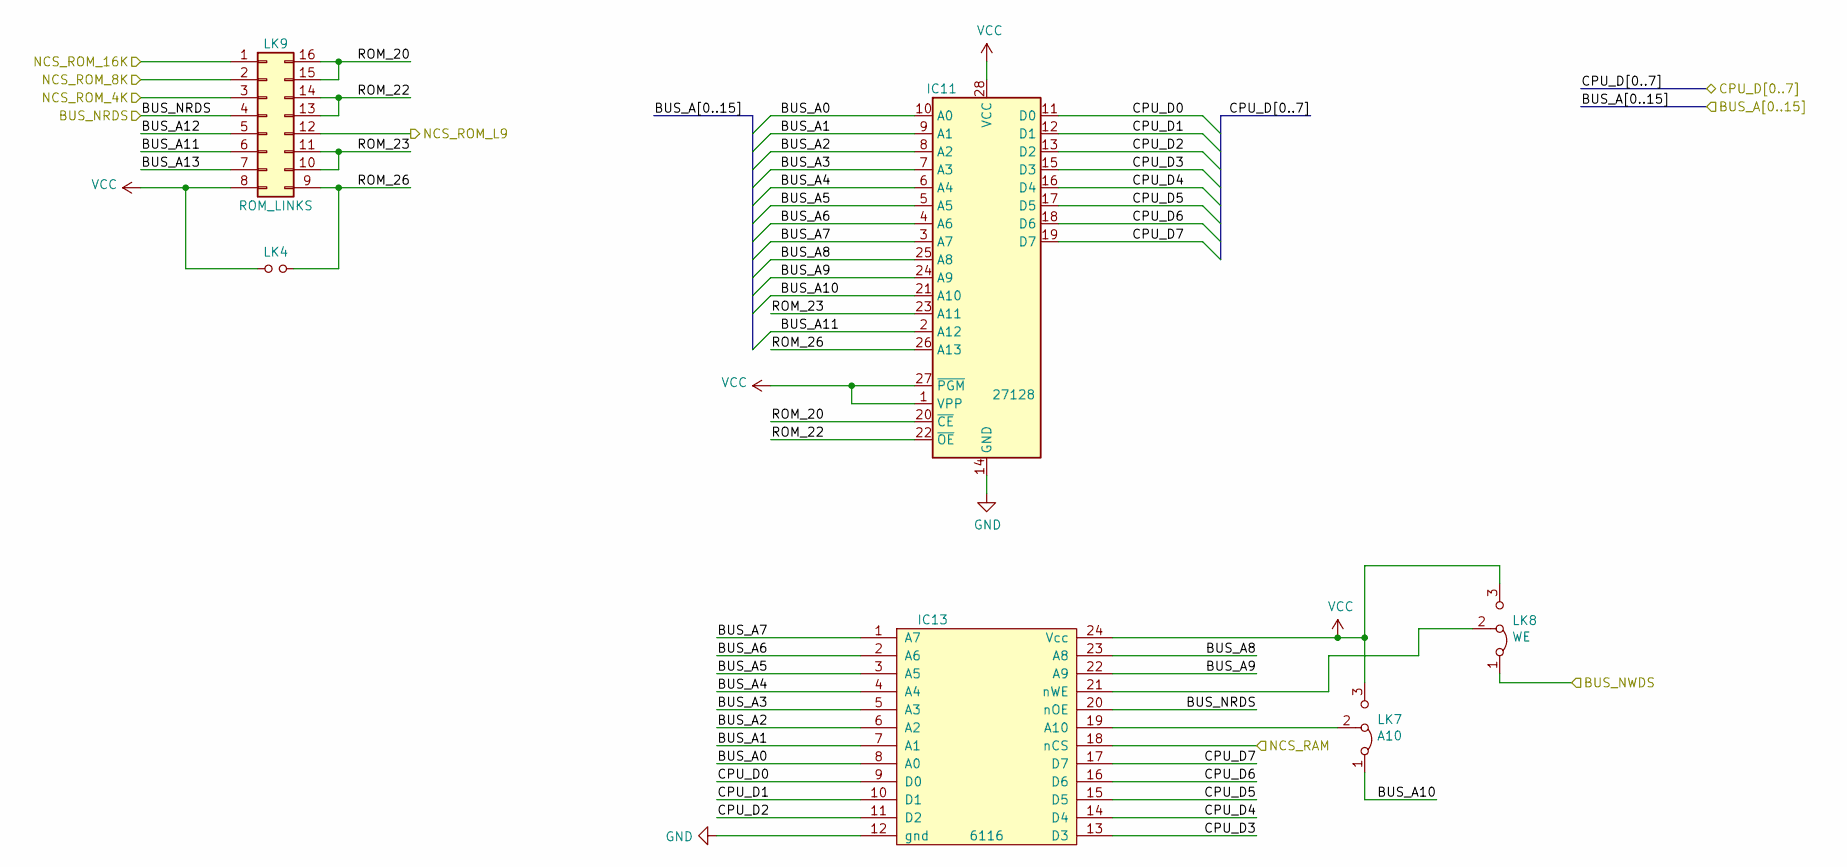
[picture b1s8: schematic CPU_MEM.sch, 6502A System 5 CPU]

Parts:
IC11: 27128; DIP-28_W15.24mm_Socket
IC13: 6116; DIP-24_W15.24mm
LK4: Jumper_NO_Small; Pin_Header_Straight_1x02_Pitch2.54mm-tight
LK7: A10; Pin_Header_Straight_1x03_Pitch2.54mm_tight_NC12
LK8: WE; Pin_Header_Straight_1x03_Pitch2.54mm_tight_NC12
LK9: ROM_LINKS; DIP-16_W7.62mm_Socket

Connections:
/BUS_NRDS: IC13.20 (nOE), LK9.4; also elsewhere on the board
/BUS_NWDS: LK8.1 (A); also elsewhere on the board
/CPU_6502A/BUS_A0: IC11.10 (A0), IC13.8 (A0); also elsewhere on the board
/CPU_6502A/BUS_A1: IC11.9 (A1), IC13.7 (A1); also elsewhere on the board
/CPU_6502A/BUS_A2: IC11.8 (A2), IC13.6 (A2); also elsewhere on the board
/CPU_6502A/BUS_A3: IC11.7 (A3), IC13.5 (A3); also elsewhere on the board
/CPU_6502A/BUS_A4: IC11.6 (A4), IC13.4 (A4); also elsewhere on the board
/CPU_6502A/BUS_A5: IC11.5 (A5), IC13.3 (A5); also elsewhere on the board
/CPU_6502A/BUS_A6: IC11.4 (A6), IC13.2 (A6); also elsewhere on the board
/CPU_6502A/BUS_A7: IC11.3 (A7), IC13.1 (A7); also elsewhere on the board
/CPU_6502A/BUS_A8: IC11.25 (A8), IC13.23 (A8); also elsewhere on the board
/CPU_6502A/BUS_A9: IC11.24 (A9), IC13.22 (A9); also elsewhere on the board
/CPU_6502A/BUS_A10: IC11.21 (A10), LK7.1 (A); also elsewhere on the board
/CPU_6502A/BUS_A11: IC11.2 (A12), LK9.6; also elsewhere on the board
/CPU_6502A/BUS_A12: LK9.5; also elsewhere on the board
/CPU_6502A/BUS_A13: LK9.7; also elsewhere on the board
/CPU_6502A/CPU_D0: IC11.11 (D0), IC13.9 (D0); also elsewhere on the board
/CPU_6502A/CPU_D1: IC11.12 (D1), IC13.10 (D1); also elsewhere on the board
/CPU_6502A/CPU_D2: IC11.13 (D2), IC13.11 (D2); also elsewhere on the board
/CPU_6502A/CPU_D3: IC11.15 (D3), IC13.13 (D3); also elsewhere on the board
/CPU_6502A/CPU_D4: IC11.16 (D4), IC13.14 (D4); also elsewhere on the board
/CPU_6502A/CPU_D5: IC11.17 (D5), IC13.15 (D5); also elsewhere on the board
/CPU_6502A/CPU_D6: IC11.18 (D6), IC13.16 (D6); also elsewhere on the board
/CPU_6502A/CPU_D7: IC11.19 (D7), IC13.17 (D7); also elsewhere on the board
/CPU_DEVSEL/NCS_RAM: IC13.18 (nCS); also elsewhere on the board
/CPU_DEVSEL/NCS_ROM_4K: LK9.3; also elsewhere on the board
/CPU_DEVSEL/NCS_ROM_8K: LK9.2; also elsewhere on the board
/CPU_DEVSEL/NCS_ROM_16K: LK9.1; also elsewhere on the board
/CPU_DEVSEL/NCS_ROM_L9: LK9.12; also elsewhere on the board
/CPU_MEM/ROM_20: IC11.20 (~CE), LK9.15, LK9.16
/CPU_MEM/ROM_22: IC11.22 (~OE), LK9.13, LK9.14
/CPU_MEM/ROM_23: IC11.23 (A11), LK9.10, LK9.11
/CPU_MEM/ROM_26: IC11.26 (A13), LK4.2, LK9.9
GND: IC11.14 (GND), IC13.12 (gnd); also elsewhere on the board
unnamed: IC13.19 (A10), LK7.2 (C)
unnamed: IC13.21 (nWE), LK8.2 (C)
VCC: IC11.1 (VPP), IC11.27 (~PGM), IC11.28 (VCC), IC13.24 (Vcc), LK4.1, LK7.3 (B), LK8.3 (B), LK9.8; also elsewhere on the board
